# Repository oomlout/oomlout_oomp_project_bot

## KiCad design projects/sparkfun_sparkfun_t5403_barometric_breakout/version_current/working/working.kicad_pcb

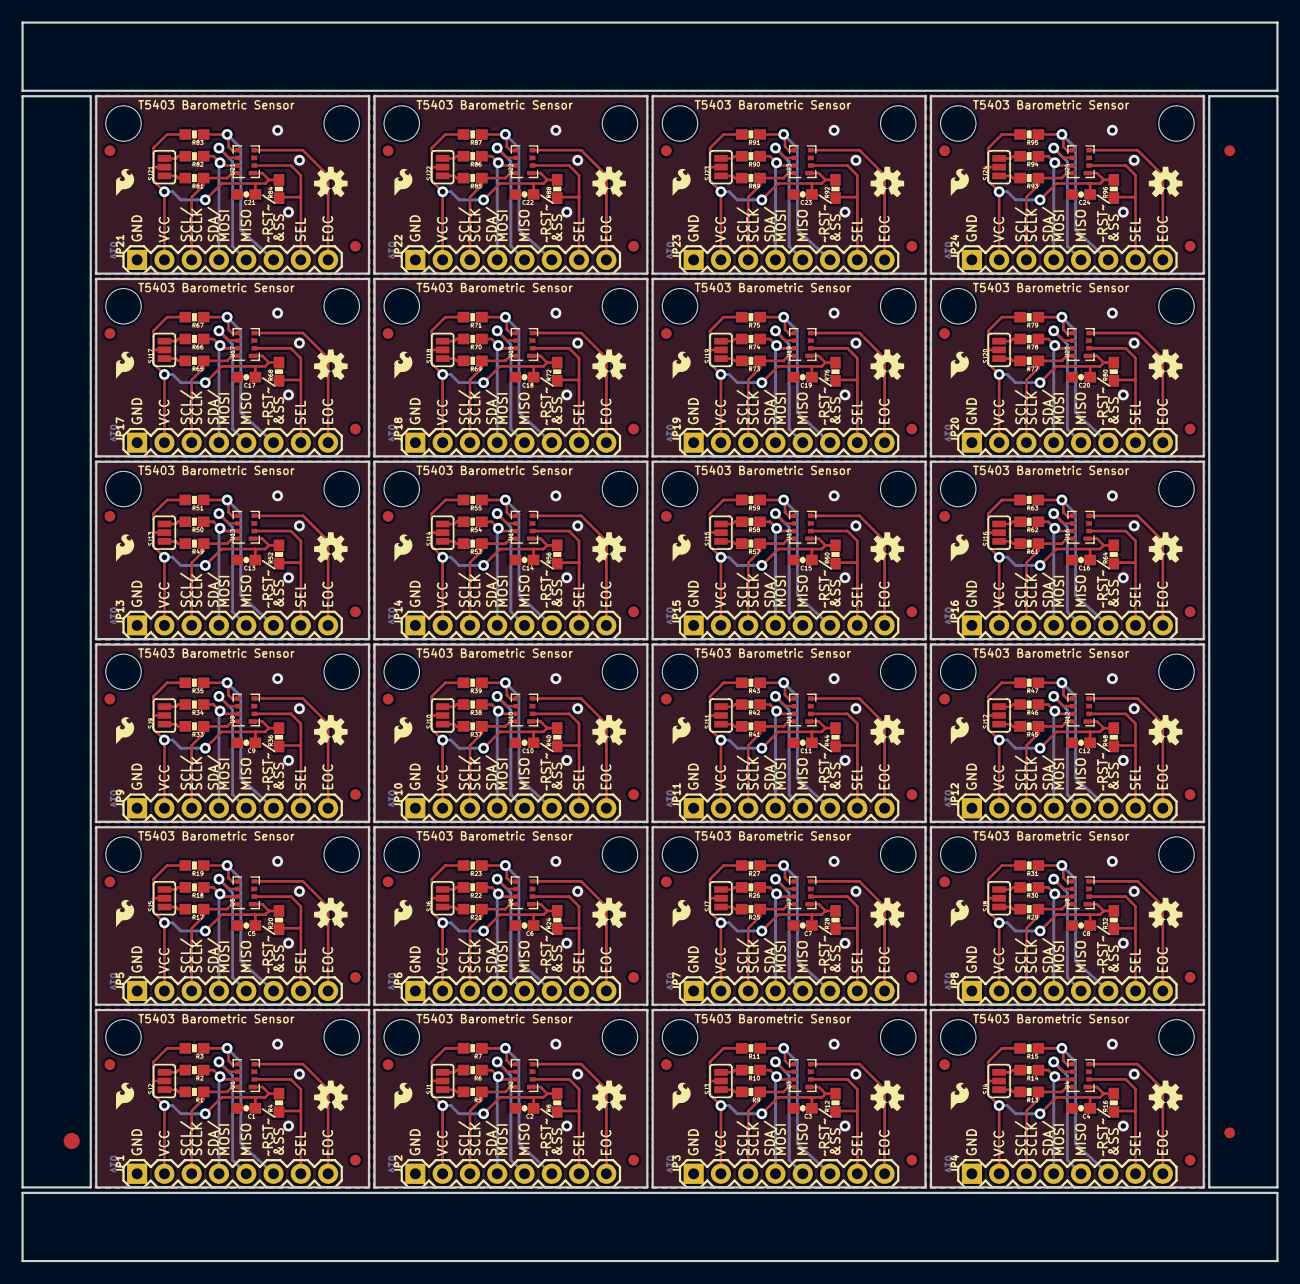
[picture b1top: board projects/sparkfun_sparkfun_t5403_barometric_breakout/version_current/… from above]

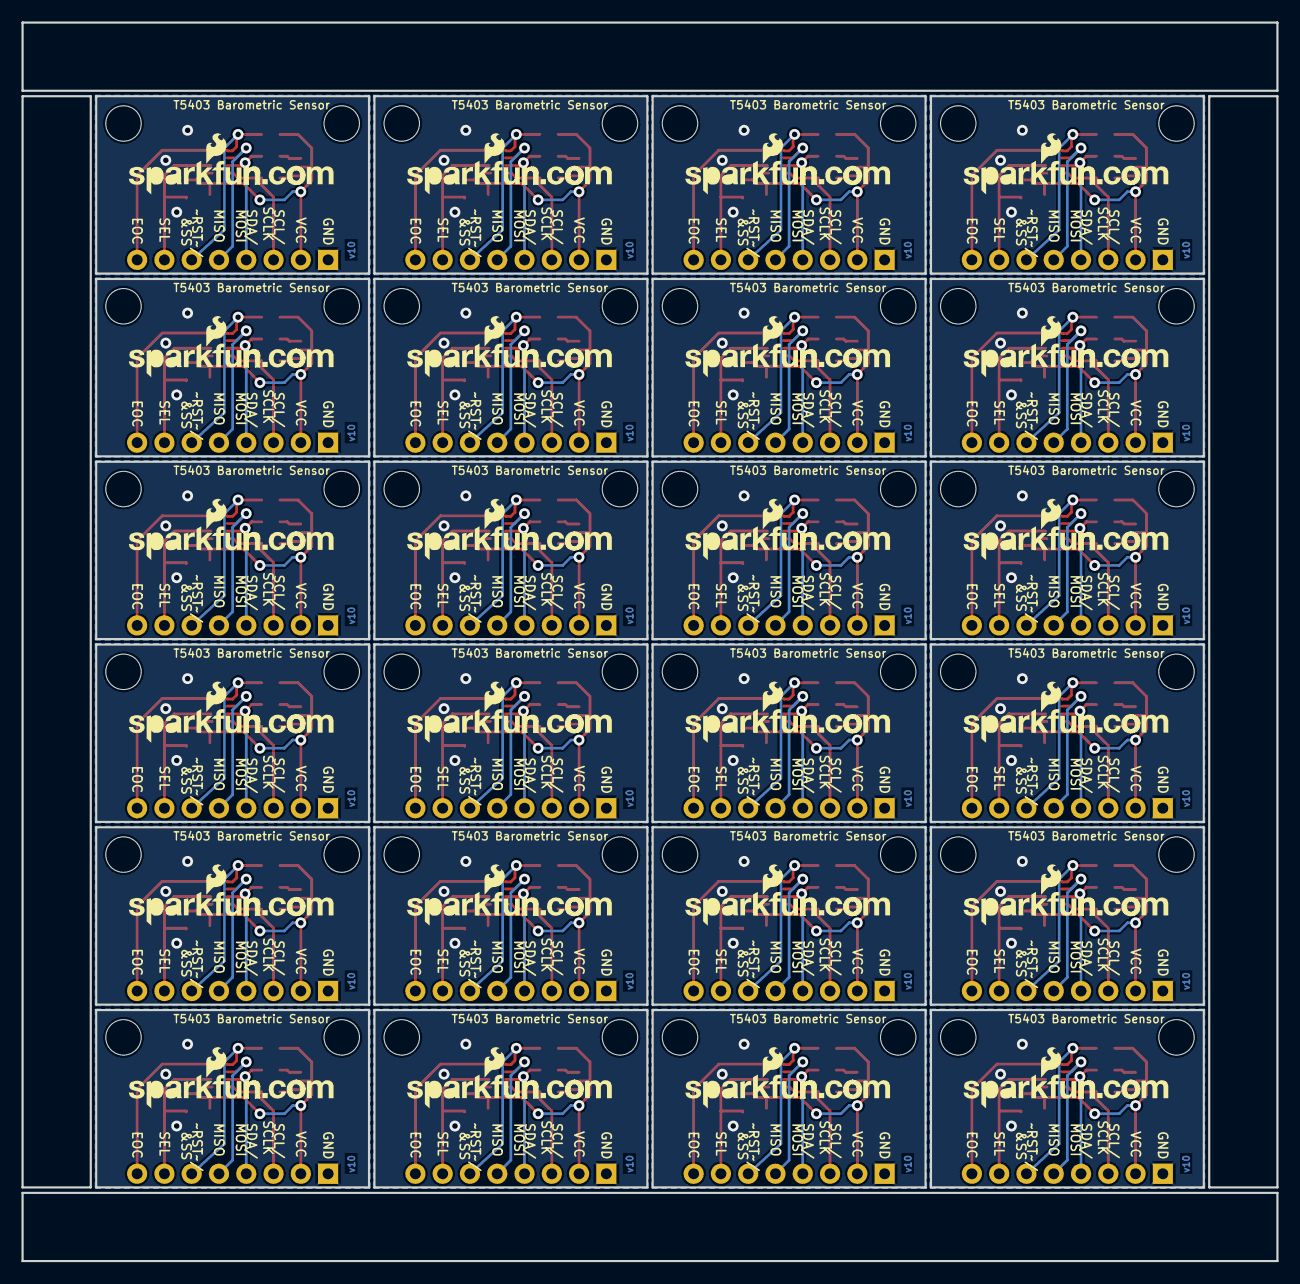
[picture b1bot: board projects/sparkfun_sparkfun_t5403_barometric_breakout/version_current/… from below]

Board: 2 copper layers, 116.8 x 115.3 mm, 363 parts (24 on the bottom side), 240 nets.

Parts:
C1, C2, C3, C4, C5, C6, C7, C8, C9, C10, C11, C12, C13, C14, C15, C16, C17, C18, C19, C20, C21, C22, C23, C24: 0.1uF; 0603-CAP
E$1: FIDUCIAL-1.5X3
E$4, E$5: FIDUCIAL-1X2
FID1, FID2, FID3, FID4, FID5, FID6, FID7, FID8, FID9, FID10, FID11, FID12, FID13, FID14, FID15, FID16, FID17, FID18, FID19, FID20, FID21, FID22, FID23, FID24, FID25, FID26, FID27, FID28, FID29, FID30, FID31, FID32, FID33, FID34, FID35, FID36, FID37, FID38, FID39, FID40, FID41, FID42, FID43, FID44, FID45, FID46, FID47, FID48: FIDUCIAL1X2; FIDUCIAL-1X2
JP1, JP2, JP3, JP4, JP5, JP6, JP7, JP8, JP9, JP10, JP11, JP12, JP13, JP14, JP15, JP16, JP17, JP18, JP19, JP20, JP21, JP22, JP23, JP24: 1X08
LOGO1, LOGO5, LOGO8, LOGO11, LOGO14, LOGO17, LOGO20, LOGO23, LOGO26, LOGO29, LOGO32, LOGO35, LOGO38, LOGO41, LOGO44, LOGO47, LOGO50, LOGO53, LOGO56, LOGO59, LOGO62, LOGO65, LOGO68, LOGO71: LOGO-SFENEW; SFE-NEW-WEBLOGO
LOGO2, LOGO4, LOGO7, LOGO10, LOGO13, LOGO16, LOGO19, LOGO22, LOGO25, LOGO28, LOGO31, LOGO34, LOGO37, LOGO40, LOGO43, LOGO46, LOGO49, LOGO52, LOGO55, LOGO58, LOGO61, LOGO64, LOGO67, LOGO70: OSHW-LOGOS; OSHW-LOGO-S
LOGO3, LOGO6, LOGO9, LOGO12, LOGO15, LOGO18, LOGO21, LOGO24, LOGO27, LOGO30, LOGO33, LOGO36, LOGO39, LOGO42, LOGO45, LOGO48, LOGO51, LOGO54, LOGO57, LOGO60, LOGO63, LOGO66, LOGO69, LOGO72: SFE_LOGO_FLAME.1_INCH; SFE_LOGO_FLAME_.1
R1, R2, R5, R6, R9, R10, R13, R14, R17, R18, R21, R22, R25, R26, R29, R30, R33, R34, R37, R38, R41, R42, R45, R46, R49, R50, R53, R54, R57, R58, R61, R62, R65, R66, R69, R70, R73, R74, R77, R78, R81, R82, R85, R86, R89, R90, R93, R94: 4.7k; 0603-RES
R3, R4, R7, R8, R11, R12, R15, R16, R19, R20, R23, R24, R27, R28, R31, R32, R35, R36, R39, R40, R43, R44, R47, R48, R51, R52, R55, R56, R59, R60, R63, R64, R67, R68, R71, R72, R75, R76, R79, R80, R83, R84, R87, R88, R91, R92, R95, R96: 10k; 0603-RES
SJ1, SJ2, SJ3, SJ4, SJ5, SJ6, SJ7, SJ8, SJ9, SJ10, SJ11, SJ12, SJ13, SJ14, SJ15, SJ16, SJ17, SJ18, SJ19, SJ20, SJ21, SJ22, SJ23, SJ24: SJ_3_PASTE1&2&3
STANDOFF1, STANDOFF2, STANDOFF3, STANDOFF4, STANDOFF5, STANDOFF6, STANDOFF7, STANDOFF8, STANDOFF9, STANDOFF10, STANDOFF11, STANDOFF12, STANDOFF13, STANDOFF14, STANDOFF15, STANDOFF16, STANDOFF17, STANDOFF18, STANDOFF19, STANDOFF20, STANDOFF21, STANDOFF22, STANDOFF23, STANDOFF24, STANDOFF25, STANDOFF26, STANDOFF27, STANDOFF28, STANDOFF29, STANDOFF30, STANDOFF31, STANDOFF32, STANDOFF33, STANDOFF34, STANDOFF35, STANDOFF36, STANDOFF37, STANDOFF38, STANDOFF39, STANDOFF40, STANDOFF41, STANDOFF42, STANDOFF43, STANDOFF44, STANDOFF45, STANDOFF46, STANDOFF47, STANDOFF48: STAND-OFF
U1, U2, U3, U4, U5, U6, U7, U8, U9, U10, U11, U12, U13, U14, U15, U16, U17, U18, U19, U20, U21, U22, U23, U24: T5400

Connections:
EOC: JP1.8, U1.4
EOC1: JP2.8, U2.4
EOC2: JP3.8, U3.4
EOC3: JP4.8, U4.4
EOC4: JP5.8, U5.4
EOC5: JP6.8, U6.4
EOC6: JP7.8, U7.4
EOC7: JP8.8, U8.4
EOC8: JP9.8, U9.4
EOC9: JP10.8, U10.4
EOC10: JP11.8, U11.4
EOC11: JP12.8, U12.4
EOC12: JP13.8, U13.4
EOC13: JP14.8, U14.4
EOC14: JP15.8, U15.4
EOC15: JP16.8, U16.4
EOC16: JP17.8, U17.4
EOC17: JP18.8, U18.4
EOC18: JP19.8, U19.4
EOC19: JP20.8, U20.4
EOC20: JP21.8, U21.4
EOC21: JP22.8, U22.4
EOC22: JP23.8, U23.4
EOC23: JP24.8, U24.4
GND: C1.2, JP1.1, U1.3
GND1: C2.2, JP2.1, U2.3
GND2: C3.2, JP3.1, U3.3
GND3: C4.2, JP4.1, U4.3
GND4: C5.2, JP5.1, U5.3
GND5: C6.2, JP6.1, U6.3
GND6: C7.2, JP7.1, U7.3
GND7: C8.2, JP8.1, U8.3
GND8: C9.2, JP9.1, U9.3
GND9: C10.2, JP10.1, U10.3
GND10: C11.2, JP11.1, U11.3
GND11: C12.2, JP12.1, U12.3
GND12: C13.2, JP13.1, U13.3
GND13: C14.2, JP14.1, U14.3
GND14: C15.2, JP15.1, U15.3
GND15: C16.2, JP16.1, U16.3
GND16: C17.2, JP17.1, U17.3
GND17: C18.2, JP18.1, U18.3
GND18: C19.2, JP19.1, U19.3
GND19: C20.2, JP20.1, U20.3
GND20: C21.2, JP21.1, U21.3
GND21: C22.2, JP22.1, U22.3
GND22: C23.2, JP23.1, U23.3
GND23: C24.2, JP24.1, U24.3
MISO: JP1.5, U1.6
MISO1: JP2.5, U2.6
MISO2: JP3.5, U3.6
MISO3: JP4.5, U4.6
MISO4: JP5.5, U5.6
MISO5: JP6.5, U6.6
MISO6: JP7.5, U7.6
MISO7: JP8.5, U8.6
MISO8: JP9.5, U9.6
MISO9: JP10.5, U10.6
MISO10: JP11.5, U11.6
MISO11: JP12.5, U12.6
MISO12: JP13.5, U13.6
MISO13: JP14.5, U14.6
MISO14: JP15.5, U15.6
MISO15: JP16.5, U16.6
MISO16: JP17.5, U17.6
MISO17: JP18.5, U18.6
MISO18: JP19.5, U19.6
MISO19: JP20.5, U20.6
MISO20: JP21.5, U21.6
MISO21: JP22.5, U22.6
MISO22: JP23.5, U23.6
MISO23: JP24.5, U24.6
unnamed: R2.2, SJ2.3
unnamed: R1.2, SJ2.1
unnamed: R6.2, SJ1.3
unnamed: R5.2, SJ1.1
unnamed: R10.2, SJ3.3
unnamed: R9.2, SJ3.1
unnamed: R14.2, SJ4.3
unnamed: R13.2, SJ4.1
unnamed: R18.2, SJ5.3
unnamed: R17.2, SJ5.1
unnamed: R22.2, SJ6.3
unnamed: R21.2, SJ6.1
unnamed: R26.2, SJ7.3
unnamed: R25.2, SJ7.1
unnamed: R30.2, SJ8.3
unnamed: R29.2, SJ8.1
unnamed: R34.2, SJ9.3
unnamed: R33.2, SJ9.1
unnamed: R38.2, SJ10.3
unnamed: R37.2, SJ10.1
unnamed: R42.2, SJ11.3
unnamed: R41.2, SJ11.1
unnamed: R46.2, SJ12.3
unnamed: R45.2, SJ12.1
unnamed: R50.2, SJ13.3
unnamed: R49.2, SJ13.1
unnamed: R54.2, SJ14.3
unnamed: R53.2, SJ14.1
unnamed: R58.2, SJ15.3
unnamed: R57.2, SJ15.1
unnamed: R62.2, SJ16.3
unnamed: R61.2, SJ16.1
unnamed: R66.2, SJ17.3
unnamed: R65.2, SJ17.1
unnamed: R70.2, SJ18.3
unnamed: R69.2, SJ18.1
unnamed: R74.2, SJ19.3
unnamed: R73.2, SJ19.1
unnamed: R78.2, SJ20.3
unnamed: R77.2, SJ20.1
unnamed: R82.2, SJ21.3
unnamed: R81.2, SJ21.1
unnamed: R86.2, SJ22.3
unnamed: R85.2, SJ22.1
unnamed: R90.2, SJ23.3
unnamed: R89.2, SJ23.1
unnamed: R94.2, SJ24.3
unnamed: R93.2, SJ24.1
SCL/SCLK: JP1.3, R1.1, U1.8
SCL/SCLK1: JP2.3, R5.1, U2.8
SCL/SCLK2: JP3.3, R9.1, U3.8
SCL/SCLK3: JP4.3, R13.1, U4.8
SCL/SCLK4: JP5.3, R17.1, U5.8
SCL/SCLK5: JP6.3, R21.1, U6.8
SCL/SCLK6: JP7.3, R25.1, U7.8
SCL/SCLK7: JP8.3, R29.1, U8.8
SCL/SCLK8: JP9.3, R33.1, U9.8
SCL/SCLK9: JP10.3, R37.1, U10.8
SCL/SCLK10: JP11.3, R41.1, U11.8
SCL/SCLK11: JP12.3, R45.1, U12.8
SCL/SCLK12: JP13.3, R49.1, U13.8
SCL/SCLK13: JP14.3, R53.1, U14.8
SCL/SCLK14: JP15.3, R57.1, U15.8
SCL/SCLK15: JP16.3, R61.1, U16.8
SCL/SCLK16: JP17.3, R65.1, U17.8
SCL/SCLK17: JP18.3, R69.1, U18.8
SCL/SCLK18: JP19.3, R73.1, U19.8
SCL/SCLK19: JP20.3, R77.1, U20.8
SCL/SCLK20: JP21.3, R81.1, U21.8
SCL/SCLK21: JP22.3, R85.1, U22.8
SCL/SCLK22: JP23.3, R89.1, U23.8
SCL/SCLK23: JP24.3, R93.1, U24.8
SDA/MOSI: JP1.4, R2.1, U1.7
SDA/MOSI1: JP2.4, R6.1, U2.7
SDA/MOSI2: JP3.4, R10.1, U3.7
SDA/MOSI3: JP4.4, R14.1, U4.7
SDA/MOSI4: JP5.4, R18.1, U5.7
SDA/MOSI5: JP6.4, R22.1, U6.7
SDA/MOSI6: JP7.4, R26.1, U7.7
SDA/MOSI7: JP8.4, R30.1, U8.7
SDA/MOSI8: JP9.4, R34.1, U9.7
SDA/MOSI9: JP10.4, R38.1, U10.7
SDA/MOSI10: JP11.4, R42.1, U11.7
SDA/MOSI11: JP12.4, R46.1, U12.7
SDA/MOSI12: JP13.4, R50.1, U13.7
SDA/MOSI13: JP14.4, R54.1, U14.7
SDA/MOSI14: JP15.4, R58.1, U15.7
SDA/MOSI15: JP16.4, R62.1, U16.7
SDA/MOSI16: JP17.4, R66.1, U17.7
SDA/MOSI17: JP18.4, R70.1, U18.7
SDA/MOSI18: JP19.4, R74.1, U19.7
SDA/MOSI19: JP20.4, R78.1, U20.7
SDA/MOSI20: JP21.4, R82.1, U21.7
SDA/MOSI21: JP22.4, R86.1, U22.7
SDA/MOSI22: JP23.4, R90.1, U23.7
SDA/MOSI23: JP24.4, R94.1, U24.7
SEL: JP1.7, R4.1, U1.2
SEL1: JP2.7, R8.1, U2.2
SEL2: JP3.7, R12.1, U3.2
SEL3: JP4.7, R16.1, U4.2
SEL4: JP5.7, R20.1, U5.2
SEL5: JP6.7, R24.1, U6.2
SEL6: JP7.7, R28.1, U7.2
SEL7: JP8.7, R32.1, U8.2
SEL8: JP9.7, R36.1, U9.2
SEL9: JP10.7, R40.1, U10.2
SEL10: JP11.7, R44.1, U11.2
SEL11: JP12.7, R48.1, U12.2
SEL12: JP13.7, R52.1, U13.2
SEL13: JP14.7, R56.1, U14.2
SEL14: JP15.7, R60.1, U15.2
SEL15: JP16.7, R64.1, U16.2
SEL16: JP17.7, R68.1, U17.2
SEL17: JP18.7, R72.1, U18.2
SEL18: JP19.7, R76.1, U19.2
SEL19: JP20.7, R80.1, U20.2
SEL20: JP21.7, R84.1, U21.2
SEL21: JP22.7, R88.1, U22.2
SEL22: JP23.7, R92.1, U23.2
SEL23: JP24.7, R96.1, U24.2
VCC: C1.1, JP1.2, R3.2, R4.2, SJ2.2, U1.1
VCC1: C2.1, JP2.2, R7.2, R8.2, SJ1.2, U2.1
VCC2: C3.1, JP3.2, R11.2, R12.2, SJ3.2, U3.1
VCC3: C4.1, JP4.2, R15.2, R16.2, SJ4.2, U4.1
VCC4: C5.1, JP5.2, R19.2, R20.2, SJ5.2, U5.1
VCC5: C6.1, JP6.2, R23.2, R24.2, SJ6.2, U6.1
VCC6: C7.1, JP7.2, R27.2, R28.2, SJ7.2, U7.1
VCC7: C8.1, JP8.2, R31.2, R32.2, SJ8.2, U8.1
VCC8: C9.1, JP9.2, R35.2, R36.2, SJ9.2, U9.1
VCC9: C10.1, JP10.2, R39.2, R40.2, SJ10.2, U10.1
VCC10: C11.1, JP11.2, R43.2, R44.2, SJ11.2, U11.1
VCC11: C12.1, JP12.2, R47.2, R48.2, SJ12.2, U12.1
VCC12: C13.1, JP13.2, R51.2, R52.2, SJ13.2, U13.1
VCC13: C14.1, JP14.2, R55.2, R56.2, SJ14.2, U14.1
VCC14: C15.1, JP15.2, R59.2, R60.2, SJ15.2, U15.1
VCC15: C16.1, JP16.2, R63.2, R64.2, SJ16.2, U16.1
VCC16: C17.1, JP17.2, R67.2, R68.2, SJ17.2, U17.1
VCC17: C18.1, JP18.2, R71.2, R72.2, SJ18.2, U18.1
VCC18: C19.1, JP19.2, R75.2, R76.2, SJ19.2, U19.1
VCC19: C20.1, JP20.2, R79.2, R80.2, SJ20.2, U20.1
VCC20: C21.1, JP21.2, R83.2, R84.2, SJ21.2, U21.1
VCC21: C22.1, JP22.2, R87.2, R88.2, SJ22.2, U22.1
VCC22: C23.1, JP23.2, R91.2, R92.2, SJ23.2, U23.1
VCC23: C24.1, JP24.2, R95.2, R96.2, SJ24.2, U24.1
~RST/&SS: JP1.6, R3.1, U1.5
~RST/&SS1: JP2.6, R7.1, U2.5
~RST/&SS2: JP3.6, R11.1, U3.5
~RST/&SS3: JP4.6, R15.1, U4.5
~RST/&SS4: JP5.6, R19.1, U5.5
~RST/&SS5: JP6.6, R23.1, U6.5
~RST/&SS6: JP7.6, R27.1, U7.5
~RST/&SS7: JP8.6, R31.1, U8.5
~RST/&SS8: JP9.6, R35.1, U9.5
~RST/&SS9: JP10.6, R39.1, U10.5
~RST/&SS10: JP11.6, R43.1, U11.5
~RST/&SS11: JP12.6, R47.1, U12.5
~RST/&SS12: JP13.6, R51.1, U13.5
~RST/&SS13: JP14.6, R55.1, U14.5
~RST/&SS14: JP15.6, R59.1, U15.5
~RST/&SS15: JP16.6, R63.1, U16.5
~RST/&SS16: JP17.6, R67.1, U17.5
~RST/&SS17: JP18.6, R71.1, U18.5
~RST/&SS18: JP19.6, R75.1, U19.5
~RST/&SS19: JP20.6, R79.1, U20.5
~RST/&SS20: JP21.6, R83.1, U21.5
~RST/&SS21: JP22.6, R87.1, U22.5
~RST/&SS22: JP23.6, R91.1, U23.5
~RST/&SS23: JP24.6, R95.1, U24.5

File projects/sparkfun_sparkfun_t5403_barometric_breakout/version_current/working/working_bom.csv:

"Id";"Designator";"Footprint";"Quantity";"Designation";"Supplier and ref";
1;"FID24,FID2,FID28,FID4,FID38,FID26,FID8,FID37,FID1,FID25,FID23,FID44,FID11,FID36,FID22,FID14,FID5,FID45,FID43,FID9,FID12,FID6,FID3,FID31,FID33,FID35,FID16,FID29,FID39,FID7,FID46,FID27,FID41,FID30,FID32,FID47,FID18,FID19,FID20,FID21,FID34,FID10,FID48,FID17,FID40,FID42,FID15,FID13";"FIDUCIAL-1X2";48;"FIDUCIAL1X2";;;
2;"R54,R69,R2,R82,R10,R77,R22,R38,R78,R53,R21,R17,R29,R66,R45,R9,R81,R70,R18,R86,R13,R62,R42,R90,R6,R46,R73,R33,R49,R93,R89,R14,R58,R25,R65,R5,R30,R37,R41,R74,R1,R34,R61,R94,R57,R50,R85,R26";"0603-RES";48;"4.7k";;;
3;"JP8,JP6,JP24,JP23,JP5,JP3,JP1,JP22,JP15,JP19,JP4,JP9,JP17,JP14,JP16,JP10,JP13,JP7,JP20,JP11,JP21,JP2,JP12,JP18";"1X08";24;"";;;
4;"C10,C16,C23,C11,C2,C12,C9,C22,C24,C6,C14,C13,C15,C8,C5,C21,C17,C19,C3,C18,C20,C7,C4,C1";"0603-CAP";24;"0.1uF";;;
5;"SJ21,SJ13,SJ16,SJ4,SJ24,SJ19,SJ20,SJ14,SJ8,SJ17,SJ15,SJ10,SJ6,SJ7,SJ9,SJ5,SJ1,SJ2,SJ11,SJ18,SJ22,SJ23,SJ3,SJ12";"SJ_3_PASTE1&2&3";24;"";;;
6;"R23,R27,R55,R47,R68,R44,R35,R7,R91,R15,R19,R36,R8,R20,R59,R3,R63,R72,R96,R87,R71,R28,R40,R43,R64,R31,R67,R11,R16,R12,R83,R75,R80,R60,R48,R88,R39,R51,R24,R52,R56,R4,R76,R84,R92,R79,R32,R95";"0603-RES";48;"10k";;;
7;"STANDOFF30,STANDOFF3,STANDOFF22,STANDOFF35,STANDOFF15,STANDOFF7,STANDOFF4,STANDOFF29,STANDOFF26,STANDOFF21,STANDOFF1,STANDOFF11,STANDOFF18,STANDOFF47,STANDOFF17,STANDOFF43,STANDOFF37,STANDOFF45,STANDOFF19,STANDOFF31,STANDOFF13,STANDOFF25,STANDOFF36,STANDOFF8,STANDOFF2,STANDOFF41,STANDOFF10,STANDOFF40,STANDOFF23,STANDOFF39,STANDOFF20,STANDOFF38,STANDOFF12,STANDOFF48,STANDOFF9,STANDOFF46,STANDOFF34,STANDOFF14,STANDOFF42,STANDOFF28,STANDOFF5,STANDOFF44,STANDOFF24,STANDOFF32,STANDOFF16,STANDOFF6,STANDOFF27,STANDOFF33";"STAND-OFF";48;"STAND-OFF";;;
8;"LOGO72,LOGO27,LOGO9,LOGO57,LOGO33,LOGO21,LOGO60,LOGO42,LOGO12,LOGO48,LOGO36,LOGO45,LOGO18,LOGO24,LOGO39,LOGO30,LOGO63,LOGO69,LOGO51,LOGO15,LOGO6,LOGO66,LOGO3,LOGO54";"SFE_LOGO_FLAME_.1";24;"SFE_LOGO_FLAME.1_INCH";;;
9;"U5,U21,U12,U20,U24,U11,U10,U7,U15,U8,U19,U3,U18,U16,U4,U17,U13,U9,U14,U23,U22,U2,U1,U6";"T5400";24;"T5400";;;
10;"LOGO22,LOGO19,LOGO37,LOGO4,LOGO28,LOGO13,LOGO34,LOGO43,LOGO49,LOGO10,LOGO64,LOGO31,LOGO40,LOGO55,LOGO61,LOGO16,LOGO70,LOGO46,LOGO25,LOGO7,LOGO2,LOGO52,LOGO58,LOGO67";"OSHW-LOGO-S";24;"OSHW-LOGOS";;;
11;"E$4,E$5";"FIDUCIAL-1X2";2;"";;;
12;"E$1";"FIDUCIAL-1.5X3";1;"";;;
13;"LOGO62,LOGO59,LOGO50,LOGO32,LOGO14,LOGO38,LOGO29,LOGO5,LOGO35,LOGO17,LOGO68,LOGO47,LOGO20,LOGO8,LOGO71,LOGO23,LOGO11,LOGO26,LOGO44,LOGO41,LOGO53,LOGO1,LOGO65,LOGO56";"SFE-NEW-WEBLOGO";24;"LOGO-SFENEW";;;

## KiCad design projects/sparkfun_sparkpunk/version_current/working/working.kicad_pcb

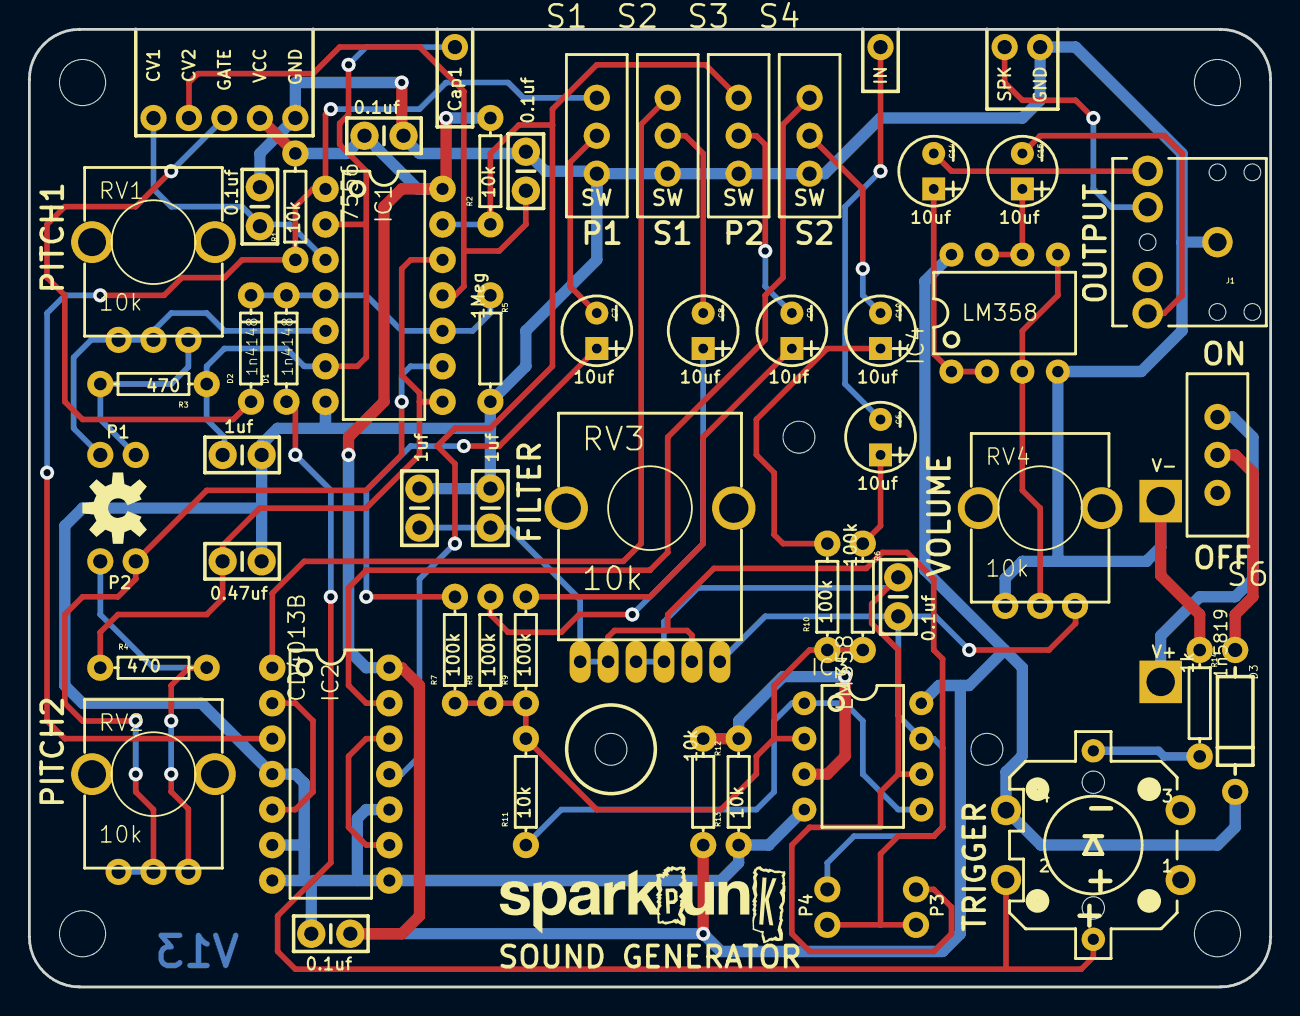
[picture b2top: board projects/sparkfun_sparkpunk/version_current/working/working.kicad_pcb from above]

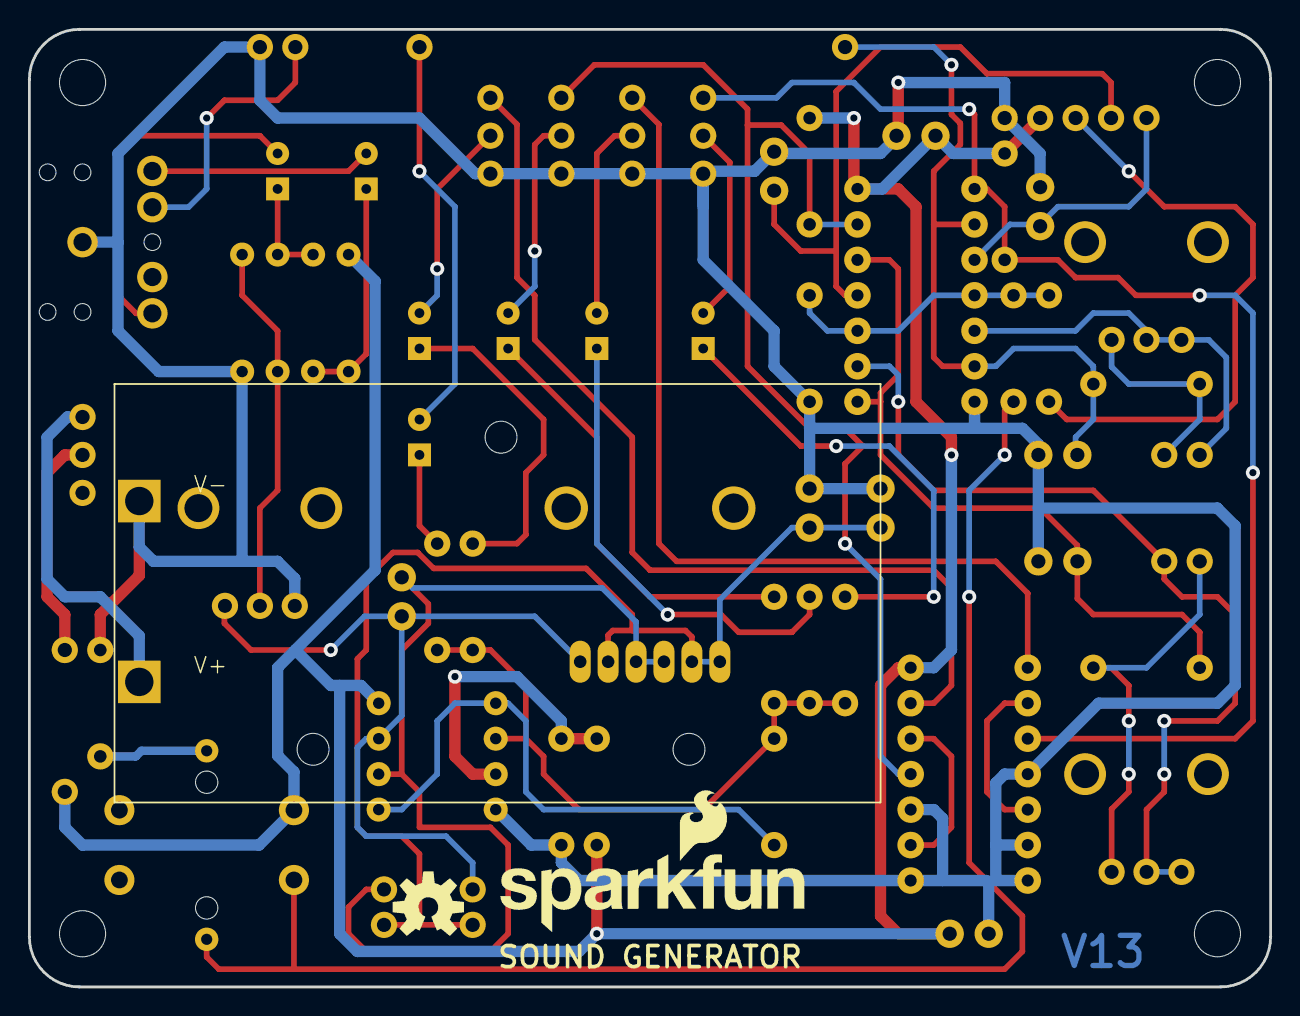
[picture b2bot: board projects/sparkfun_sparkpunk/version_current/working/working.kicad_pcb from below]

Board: 2 copper layers, 88.9 x 68.6 mm, 75 parts (3 on the bottom side), 44 nets.

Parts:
BAT1: 9V; BC9VPC_KIT
C1, C2, C5, C11, C16: .1uf; CAP-PTH-SMALL-KIT
C3, C12, C13: 1uf; CAP-PTH-SMALL-KIT
C4: .47uf; CAP-PTH-SMALL-KIT
C6, C7, C8, C9, C10, C14, C15: 10uf/25V; CPOL-RADIAL-10UF-25V-KIT
D1, D2: 1n4148; DIODE-1N4148-KIT
D3: 1n5819; DIODE-1N4001-KIT
FRAME1: FRAME-LEDGER; CREATIVE_COMMONS
IC1: 7556; DIL14-KIT
IC2: CD4013B; DIL14-KIT
IC3, IC4: LM358; DIP08-KIT
J1: AUDIO-JACK2KIT; AUDIO-JACK-KIT
JP1: CV1; 1X01NS
JP2: CV2; 1X01NS
JP3, JP4: P1; 1X01NS
JP5, JP6: P2; 1X01NS
JP7: CAP1; 1X01NS
JP8: GATE; 1X01NS
JP9: IN; 1X01NS
JP10, JP11: P3; 1X01NS
JP12, JP13: P4; 1X01NS
JP14: SPK; 1X01NS
JP15, JP17: GND; 1X01NS
JP16: VCC; 1X01NS
LOGO1: SFE_LOGO_NAME_FLAME.2_INCH; SFE_LOGO_NAME_FLAME_.2
LOGO2: SPARKPUNK_LOGO.1INCH_TALL; SPARKPUNK_LOGO_.1
LOGO3, LOGO4: OSHW-LOGOM; OSHW-LOGO-M
R1, R2, R11, R12, R13: 10k; AXIAL-0.3EZ
R3, R4: 470; AXIAL-0.3EZ
R5: 1Meg; AXIAL-0.3EZ
R6, R7, R8, R9, R10: 100k; AXIAL-0.3EZ
R14: 1k; AXIAL-0.3EZ
RV1, RV2, RV4: 10k; ALPS_POT_KIT
RV3: 10k; POT_PANASONIC_DUAL_VERT_KIT
S1, S2, S3, S4, S6: SPDT; SWITCH-SPDT_KIT
S5: SWITCH-MOMENTARY-LEDEZ; TACTILE-PTH-LED-12MM-EZ
STANDOFF1, STANDOFF2, STANDOFF3, STANDOFF4: STAND-OFF

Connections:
BUTTON: D1.A, S5.2, S5.A
FILT-OUT: C11.2, IC3.7, JP13.1, RV3.A3, RV4.P$3
GND: BAT1.V-, C1.2, C2.2, C3.1, C4.2, C5.2, C12.1, C13.2, C16.2, IC1.7, IC2.4, IC2.6, IC2.7, IC2.8, IC2.10, IC3.4, IC4.4, J1.SLEEVE, JP15.1, JP17.1, R5.P$2, R13.P$1, R14.P$1, RV4.P$1, S1.3, S2.3, S3.3, S4.3
N: IC4.3, IC4.5, RV4.P$2
unnamed: D2.A, JP8.1
unnamed: C4.1, IC1.8, IC1.12, R4.P$1
unnamed: D1.C, D2.C, IC1.4, IC1.10, R5.P$1
unnamed: D3.A, S6.2
unnamed: JP6.1, R4.P$2, RV2.P$3
unnamed: R14.P$2, S5.C
unnamed: IC2.2, IC2.5
unnamed: IC2.9, IC2.12
unnamed: JP4.1, R3.P$2, RV1.P$3
unnamed: C10.2, S4.2
unnamed: J1.TSH, JP14.1
unnamed: C14.1, IC4.1, IC4.2
unnamed: C15.2, J1.RING
unnamed: C10.1, R10.P$2
unnamed: C9.1, R9.P$2
unnamed: C9.2, S3.2
unnamed: C6.2, JP9.1
unnamed: C6.1, R6.P$1
unnamed: C7.2, S1.2
unnamed: C8.2, S2.2
unnamed: C15.1, IC4.6, IC4.7
unnamed: IC3.2, R6.P$2, R7.P$1, R8.P$1, R9.P$1, R10.P$1, R11.P$2
unnamed: IC3.1, IC3.5, R11.P$1
unnamed: C8.1, R8.P$2
unnamed: C7.1, R7.P$2
unnamed: C14.2, J1.TIP
unnamed: C11.1, IC3.6, JP10.1, RV3.B1, RV3.B2
unnamed: C12.2, C13.1, JP11.1, JP12.1, RV3.A1, RV3.A2, RV3.B3
PITCH1: IC1.1, IC2.3, R1.P$1, S1.1
PITCH2: IC1.13, IC2.11, R2.P$1, S3.1
POT1: IC1.5, JP3.1, RV1.P$1, RV1.P$2
POT2: IC1.9, JP5.1, RV2.P$1, RV2.P$2
SUB1: IC2.1, S2.1
SUB2: IC2.13, S4.1
VBATT: BAT1.V+, S6.3
VCAP1: C3.2, IC1.2, IC1.6, JP7.1, R3.P$1
VCC: C5.1, C16.1, D3.C, IC1.14, IC2.14, IC3.8, IC4.8, JP16.1, R1.P$2, R2.P$2, R12.P$2, S5.4
VCC1: C2.1, IC1.11, JP2.1
VCC2: C1.1, IC1.3, JP1.1
VREF: IC3.3, R12.P$1, R13.P$2

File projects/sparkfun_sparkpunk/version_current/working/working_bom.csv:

"Id";"Designator";"Footprint";"Quantity";"Designation";"Supplier and ref";
1;"R14";"AXIAL-0.3EZ";1;"1k";;;
2;"C9,C6,C7,C10,C15,C8,C14";"CPOL-RADIAL-10UF-25V-KIT";7;"10uf/25V";;;
3;"JP4,JP3";"1X01NS";2;"P1";;;
4;"RV1,RV4,RV2";"ALPS_POT_KIT";3;"10k";;;
5;"JP5,JP6";"1X01NS";2;"P2";;;
6;"D2,D1";"DIODE-1N4148-KIT";2;"1n4148";;;
7;"IC2";"DIL14-KIT";1;"CD4013B";;;
8;"R8,R9,R7,R10,R6";"AXIAL-0.3EZ";5;"100k";;;
9;"STANDOFF4,STANDOFF3,STANDOFF2,STANDOFF1";"STAND-OFF";4;"STAND-OFF";;;
10;"JP15,JP17";"1X01NS";2;"GND";;;
11;"S2,S1,S3,S4,S6";"SWITCH-SPDT_KIT";5;"SPDT";;;
12;"IC3,IC4";"DIP08-KIT";2;"LM358";;;
13;"FRAME1";"CREATIVE_COMMONS";1;"FRAME-LEDGER";;;
14;"C2,C16,C11,C5,C1";"CAP-PTH-SMALL-KIT";5;".1uf";;;
15;"JP8";"1X01NS";1;"GATE";;;
16;"C4";"CAP-PTH-SMALL-KIT";1;".47uf";;;
17;"LOGO2";"SPARKPUNK_LOGO_.1";1;"SPARKPUNK_LOGO.1INCH_TALL";;;
18;"JP13,JP12";"1X01NS";2;"P4";;;
19;"R3,R4";"AXIAL-0.3EZ";2;"470";;;
20;"C3,C13,C12";"CAP-PTH-SMALL-KIT";3;"1uf";;;
21;"JP10,JP11";"1X01NS";2;"P3";;;
22;"J1";"AUDIO-JACK-KIT";1;"AUDIO-JACK2KIT";;;
23;"IC1";"DIL14-KIT";1;"7556";;;
24;"D3";"DIODE-1N4001-KIT";1;"1n5819";;;
25;"JP14";"1X01NS";1;"SPK";;;
26;"JP7";"1X01NS";1;"CAP1";;;
27;"RV3";"POT_PANASONIC_DUAL_VERT_KIT";1;"10k";;;
28;"JP9";"1X01NS";1;"IN";;;
29;"S5";"TACTILE-PTH-LED-12MM-EZ";1;"SWITCH-MOMENTARY-LEDEZ";;;
30;"JP16";"1X01NS";1;"VCC";;;
31;"LOGO3,LOGO4";"OSHW-LOGO-M";2;"OSHW-LOGOM";;;
32;"JP2";"1X01NS";1;"CV2";;;
33;"R1,R13,R11,R12,R2";"AXIAL-0.3EZ";5;"10k";;;
34;"JP1";"1X01NS";1;"CV1";;;
35;"R5";"AXIAL-0.3EZ";1;"1Meg";;;
36;"BAT1";"BC9VPC_KIT";1;"9V";;;
37;"LOGO1";"SFE_LOGO_NAME_FLAME_.2";1;"SFE_LOGO_NAME_FLAME.2_INCH";;;

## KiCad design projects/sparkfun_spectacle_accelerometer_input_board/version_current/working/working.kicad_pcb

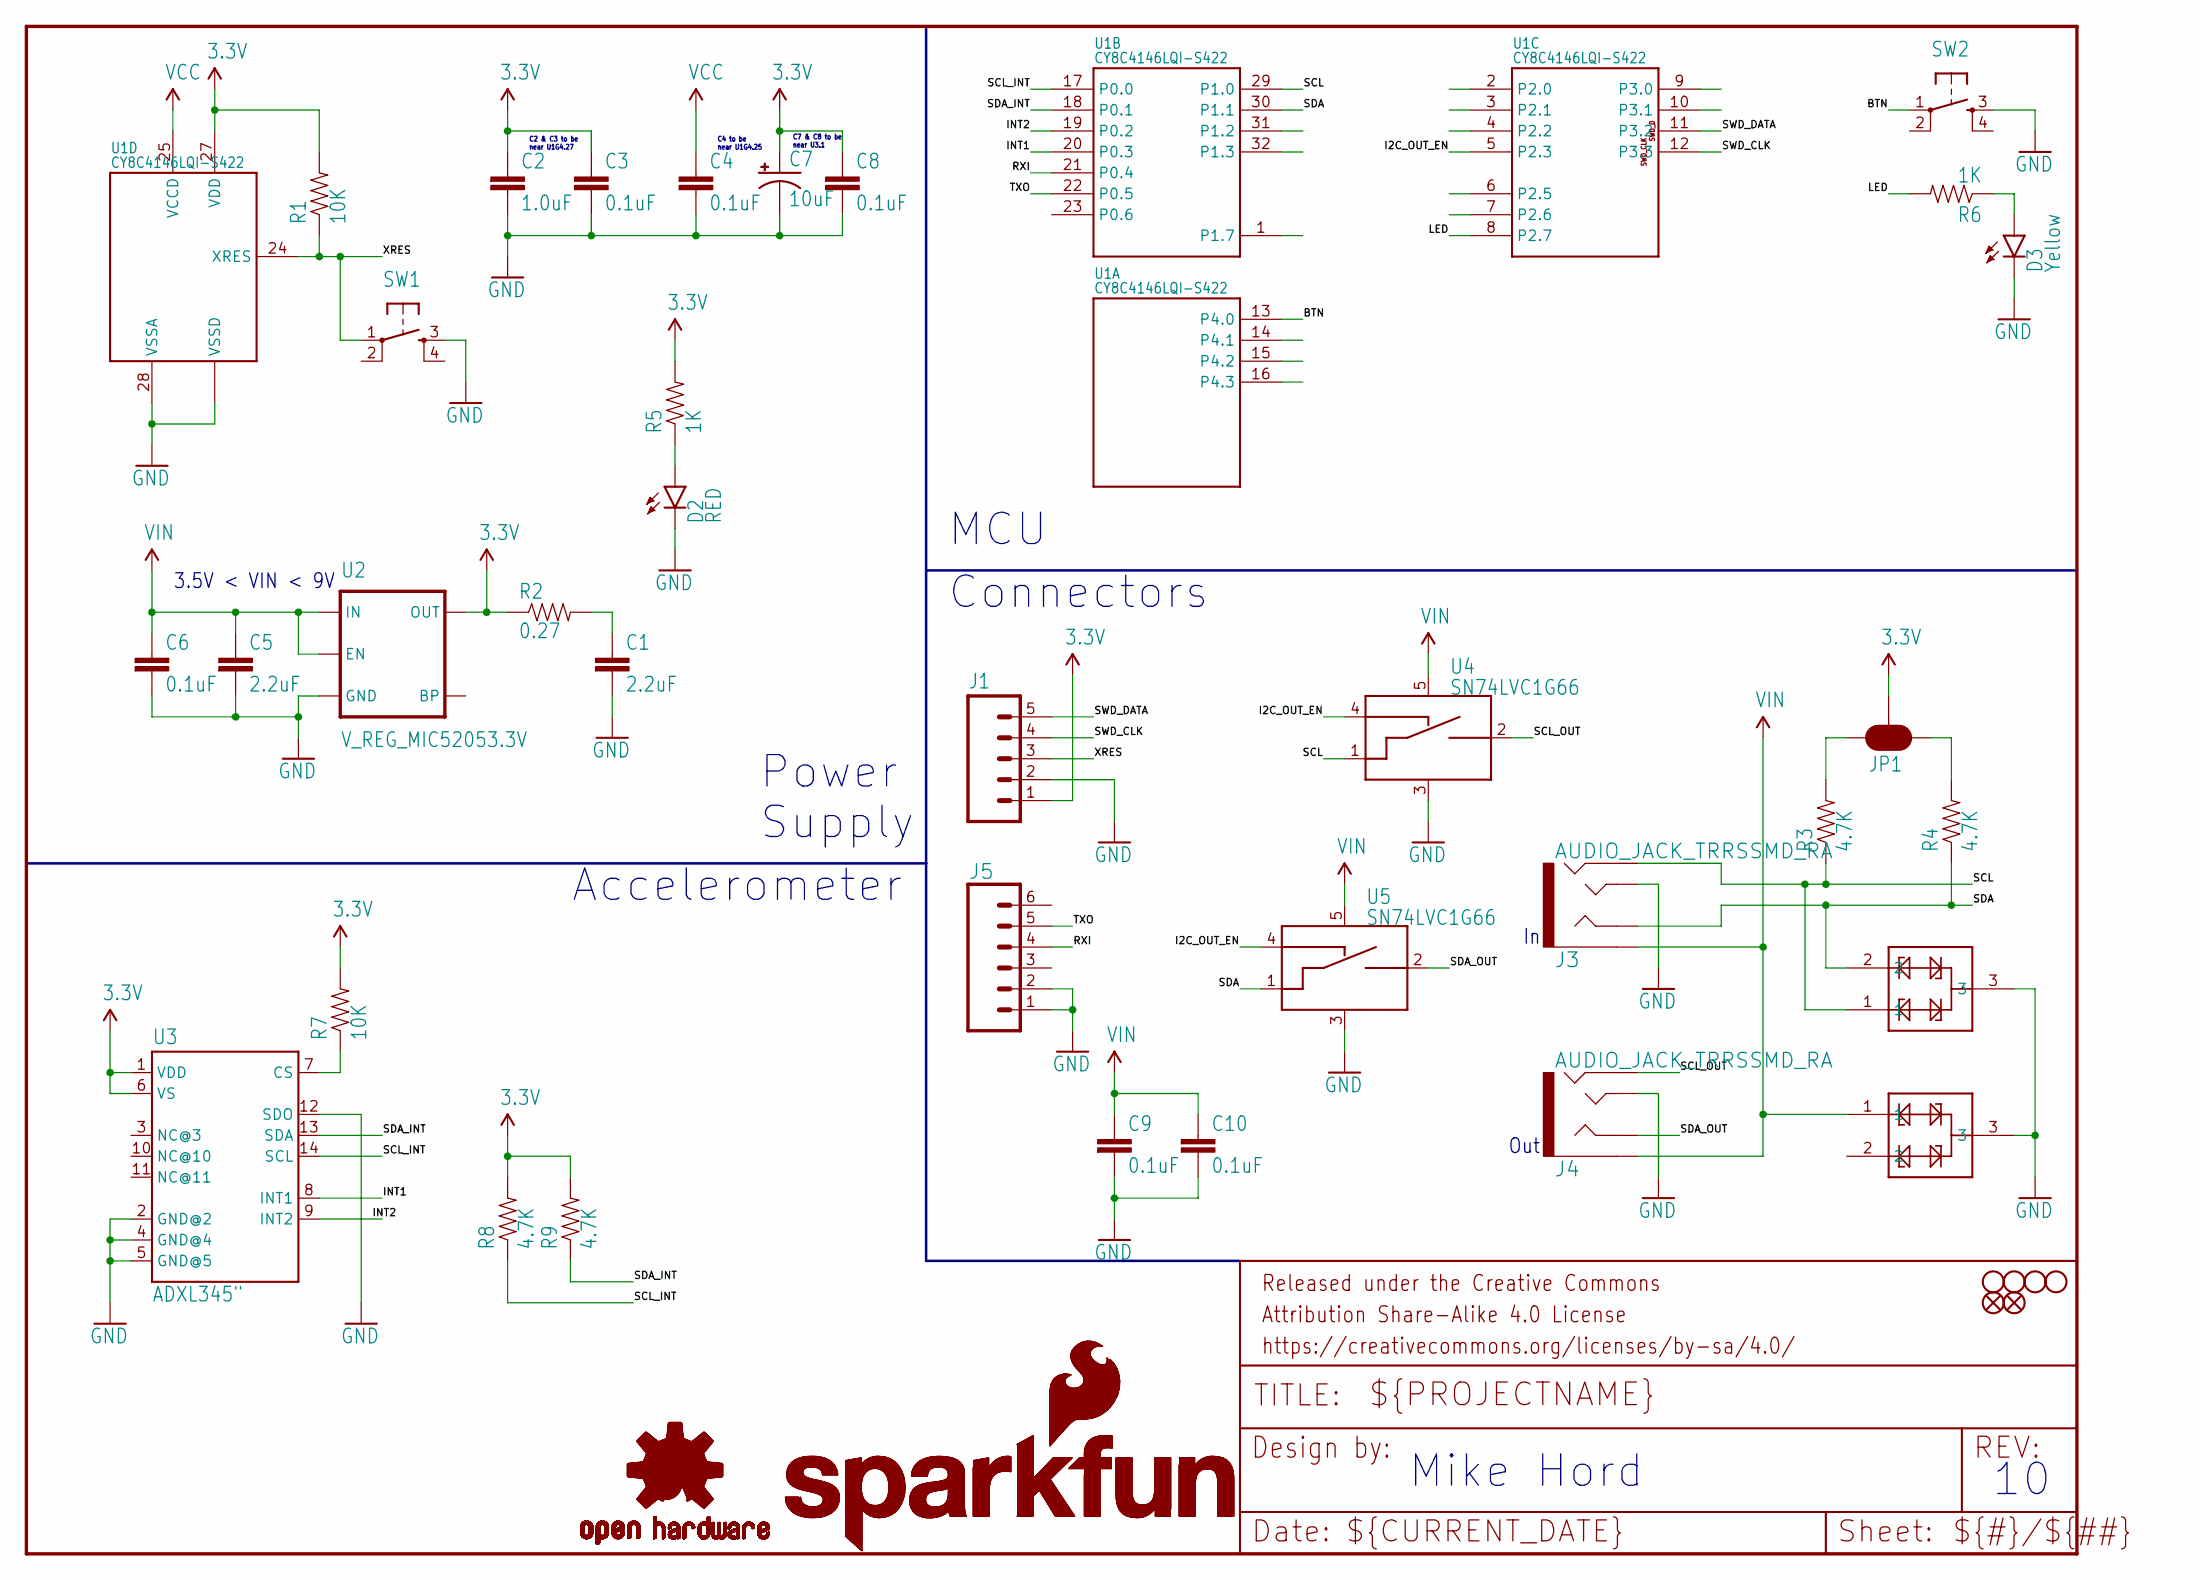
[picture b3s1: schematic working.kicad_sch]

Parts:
C1, C5: 2.2uF; 0603-CAP
C2: 1.0uF; 0402-CAP
C3, C4, C6, C8, C9, C10: 0.1uF; 0402-CAP
C7: 10uF; EIA3216
D2: RED; LED-0603
D3: Yellow; LED-0603
D4, D5: PESD1CAN; SOT23-3
FD1, FD2: FIDUCIALUFIDUCIAL; MICRO-FIDUCIAL
FRAME1: FRAME-LETTER; CREATIVE_COMMONS
H1, H2, H3, H4: STAND-OFF
J1: M05NO_SILK; 1X05_NO_SILK
J3, J4: AUDIO_JACK_TRRSSMD_RA; AUDIO_JACK_3.5MM_TRRS_SMD_RA
J5: CONN_06NO_SILK_NO_POP; 1X06_NO_SILK
JP1: JUMPER-PAD-3-NC_BY_PASTE; PAD-JUMPER-3-NC_BY_PASTE_YES_SILK_FULL_BOX
LOGO1, LOGO4: SFE_LOGO_NAME_FLAME.1_INCH; SFE_LOGO_NAME_FLAME_.1
LOGO2, LOGO3: OSHW-LOGOS; OSHW-LOGO-S
R1, R7: 10K; 0603-RES
R2: 0.27; 0603-RES
R3, R4, R8, R9: 4.7K; 0603-RES
R5, R6: 1K; 0603-RES
SW1, SW2: SWITCH_SPST_4_PINRECT; TACTILE_SWITCH_SMD_4.6X2.8MM
U1: CY8C4146LQI-S422; QFN-32
U2: V_REG_MIC52053.3V; SOT23-5
U3: ADXL345"; ADXL3451_1
U4, U5: SN74LVC1G66; SOT23-5

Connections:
3.3V: C2.1, C3.1, C7.A (+), C8.1, J1.1, JP1.2, R1.2, R2.1, R5.2, R7.2, R8.2, R9.2, U1.27 (VDD), U2.5 (OUT), U3.1 (VDD), U3.6 (VS)
BTN: SW2.1, U1.13 (P4.0)
GND: C1.2, C2.2, C3.2, C4.2, C5.2, C6.2, C7.C (-), C8.2, C9.2, C10.2, D2.C, D3.C, D4.3, D5.3, J1.2, J3.TIP, J4.TIP, J5.1, J5.2, SW1.3, SW2.3, U1.26 (VSSD), U1.28 (VSSA), U1.EP (VSSD), U2.2 (GND), U3.2 (GND@2), U3.4 (GND@4), U3.5 (GND@5), U3.12 (SDO), U4.3 (VSS), U5.3 (VSS)
I2C_OUT_EN: U1.5 (P2.3), U4.4 (CTRL_IN), U5.4 (CTRL_IN)
INT1: U1.20 (P0.3), U3.8 (INT1)
INT2: U1.19 (P0.2), U3.9 (INT2)
LED: R6.2, U1.8 (P2.7)
unnamed: JP1.3, R3.2
unnamed: C1.1, R2.2
unnamed: D2.A, R5.1
unnamed: D3.A, R6.1
unnamed: JP1.1, R4.2
unnamed: R7.1, U3.7 (CS)
RXI: J5.4, U1.21 (P0.4)
SCL: D4.1, J3.RING2, R3.1, U1.29 (P1.0), U4.1 (A_IN)
SCL_INT: R8.1, U1.17 (P0.0), U3.14 (SCL)
SCL_OUT: J4.RING2, U4.2 (A_OUT)
SDA: D4.2, J3.RING1, R4.1, U1.30 (P1.1), U5.1 (A_IN)
SDA_INT: R9.1, U1.18 (P0.1), U3.13 (SDA)
SDA_OUT: J4.RING1, U5.2 (A_OUT)
SWD_CLK: J1.4, U1.12 (P3.3)
SWD_DATA: J1.5, U1.11 (P3.2)
TXO: J5.5, U1.22 (P0.5)
VCC: C4.1, U1.25 (VCCD)
VIN: C5.1, C6.1, C9.1, C10.1, D5.1, J3.EARTH, J4.EARTH, U2.1 (IN), U2.3 (EN), U4.5 (VCC), U5.5 (VCC)
XRES: J1.3, R1.1, SW1.1, U1.24 (XRES)

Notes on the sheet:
3.5V < VIN < 9V
C7 & C8 to be near U3.1
C2 & C3 to be near U1G4.27
Mike Hord
C4 to be near U1G4.25
MCU
Out
Power Supply
Connectors
Accelerometer

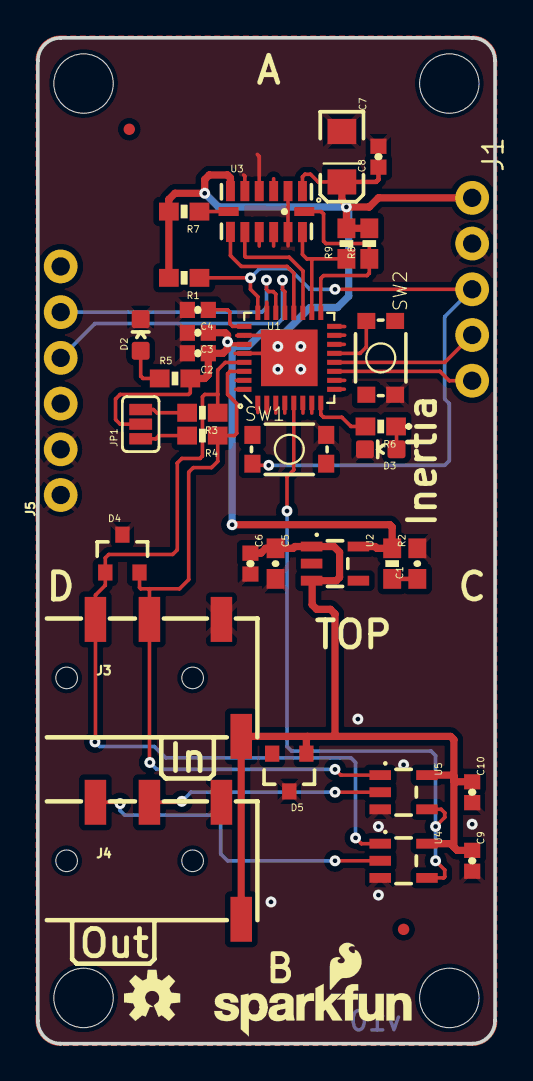
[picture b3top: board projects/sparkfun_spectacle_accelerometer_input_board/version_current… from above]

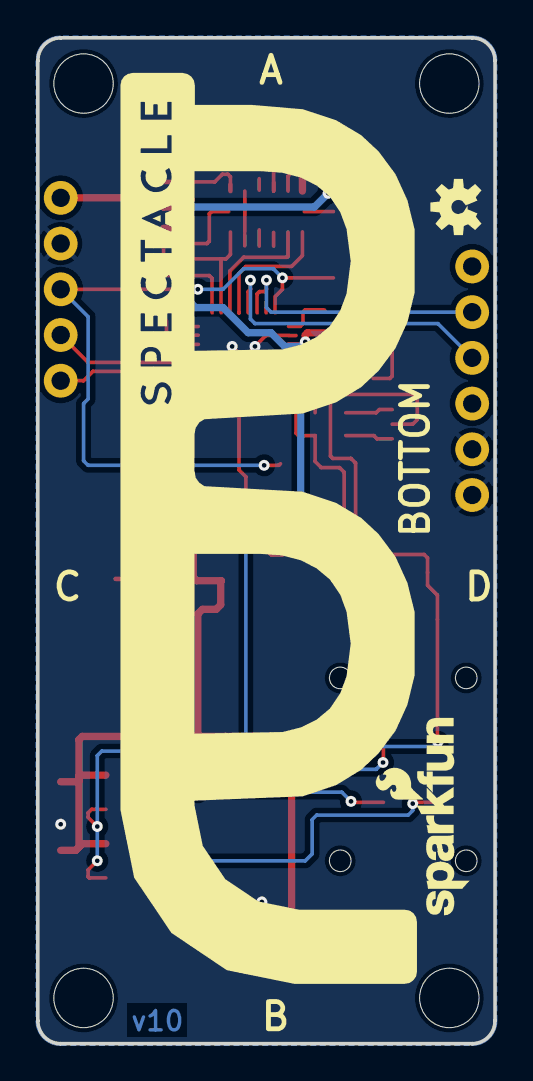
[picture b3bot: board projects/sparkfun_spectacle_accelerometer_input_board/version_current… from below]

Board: 4 copper layers, 25.4 x 55.9 mm, 47 parts (3 on the bottom side), 26 nets.

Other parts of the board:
U$4: SPECTACLE_LOGO_NEGATIVE_2.2X1.0

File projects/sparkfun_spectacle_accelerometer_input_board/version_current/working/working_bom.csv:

"Id";"Designator";"Footprint";"Quantity";"Designation";"Supplier and ref";
1;"C6,C8,C10,C4,C3,C9";"0402-CAP";6;"0.1uF";;;
2;"D5,D4";"SOT23-3";2;"PESD1CAN";;;
3;"U2";"SOT23-5";1;"3.3V/150mA";;;
4;"J3,J4";"AUDIO_JACK_3.5MM_TRRS_SMD_RA";2;"AUDIO_JACK_TRRSSMD_RA";;;
5;"H2,H3,H1,H4";"STAND-OFF";4;"STAND-OFF";;;
6;"JP1";"PAD-JUMPER-3-NC_BY_PASTE_YES_SILK_FULL_BOX";1;"JUMPER-PAD-3-NC_BY_PASTE";;;
7;"R4,R3,R9,R8";"0603-RES";4;"4.7K";;;
8;"R5,R6";"0603-RES";2;"1K";;;
9;"FRAME1";"CREATIVE_COMMONS";1;"FRAME-LETTER";;;
10;"FD1,FD2";"MICRO-FIDUCIAL";2;"FIDUCIALUFIDUCIAL";;;
11;"U4,U5";"SOT23-5";2;"SN74LVC1G66";;;
12;"C7";"EIA3216";1;"10uF";;;
13;"C5,C1";"0603-CAP";2;"2.2uF";;;
14;"D2";"LED-0603";1;"RED";;;
15;"R2";"0603-RES";1;"0.27";;;
16;"SW1,SW2";"TACTILE_SWITCH_SMD_4.6X2.8MM";2;"";;;
17;"J5";"1X06_NO_SILK";1;"";;;
18;"C2";"0402-CAP";1;"1.0uF";;;
19;"U1";"QFN-32";1;"CY8C4146LQI-S422";;;
20;"J1";"1X05_NO_SILK";1;"";;;
21;"D3";"LED-0603";1;"Yellow";;;
22;"LOGO2,LOGO3";"OSHW-LOGO-S";2;"OSHW-LOGOS";;;
23;"U3";"ADXL3451_1";1;"ADXL345";;;
24;"LOGO1,LOGO4";"SFE_LOGO_NAME_FLAME_.1";2;"SFE_LOGO_NAME_FLAME.1_INCH";;;
25;"R7,R1";"0603-RES";2;"10K";;;
26;"U$4";"SPECTACLE_LOGO_NEGATIVE_2.2X1.0";1;"";;;

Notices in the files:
projects/sparkfun_sparkfun_rtk_reference_station/version_current/working/working.kicad_sch:
https://creativecommons.org/licenses/by-sa/4.0
Released under the Creative Commons
projects/sparkfun_sparkfun_t5403_barometric_breakout/version_current/working/working.kicad_sch:
http://creativecommons.org/licenses/by-sa/3.0
parts and their libraries:
Released under the Creative Commons Attribution Share-Alike 4.0 License
